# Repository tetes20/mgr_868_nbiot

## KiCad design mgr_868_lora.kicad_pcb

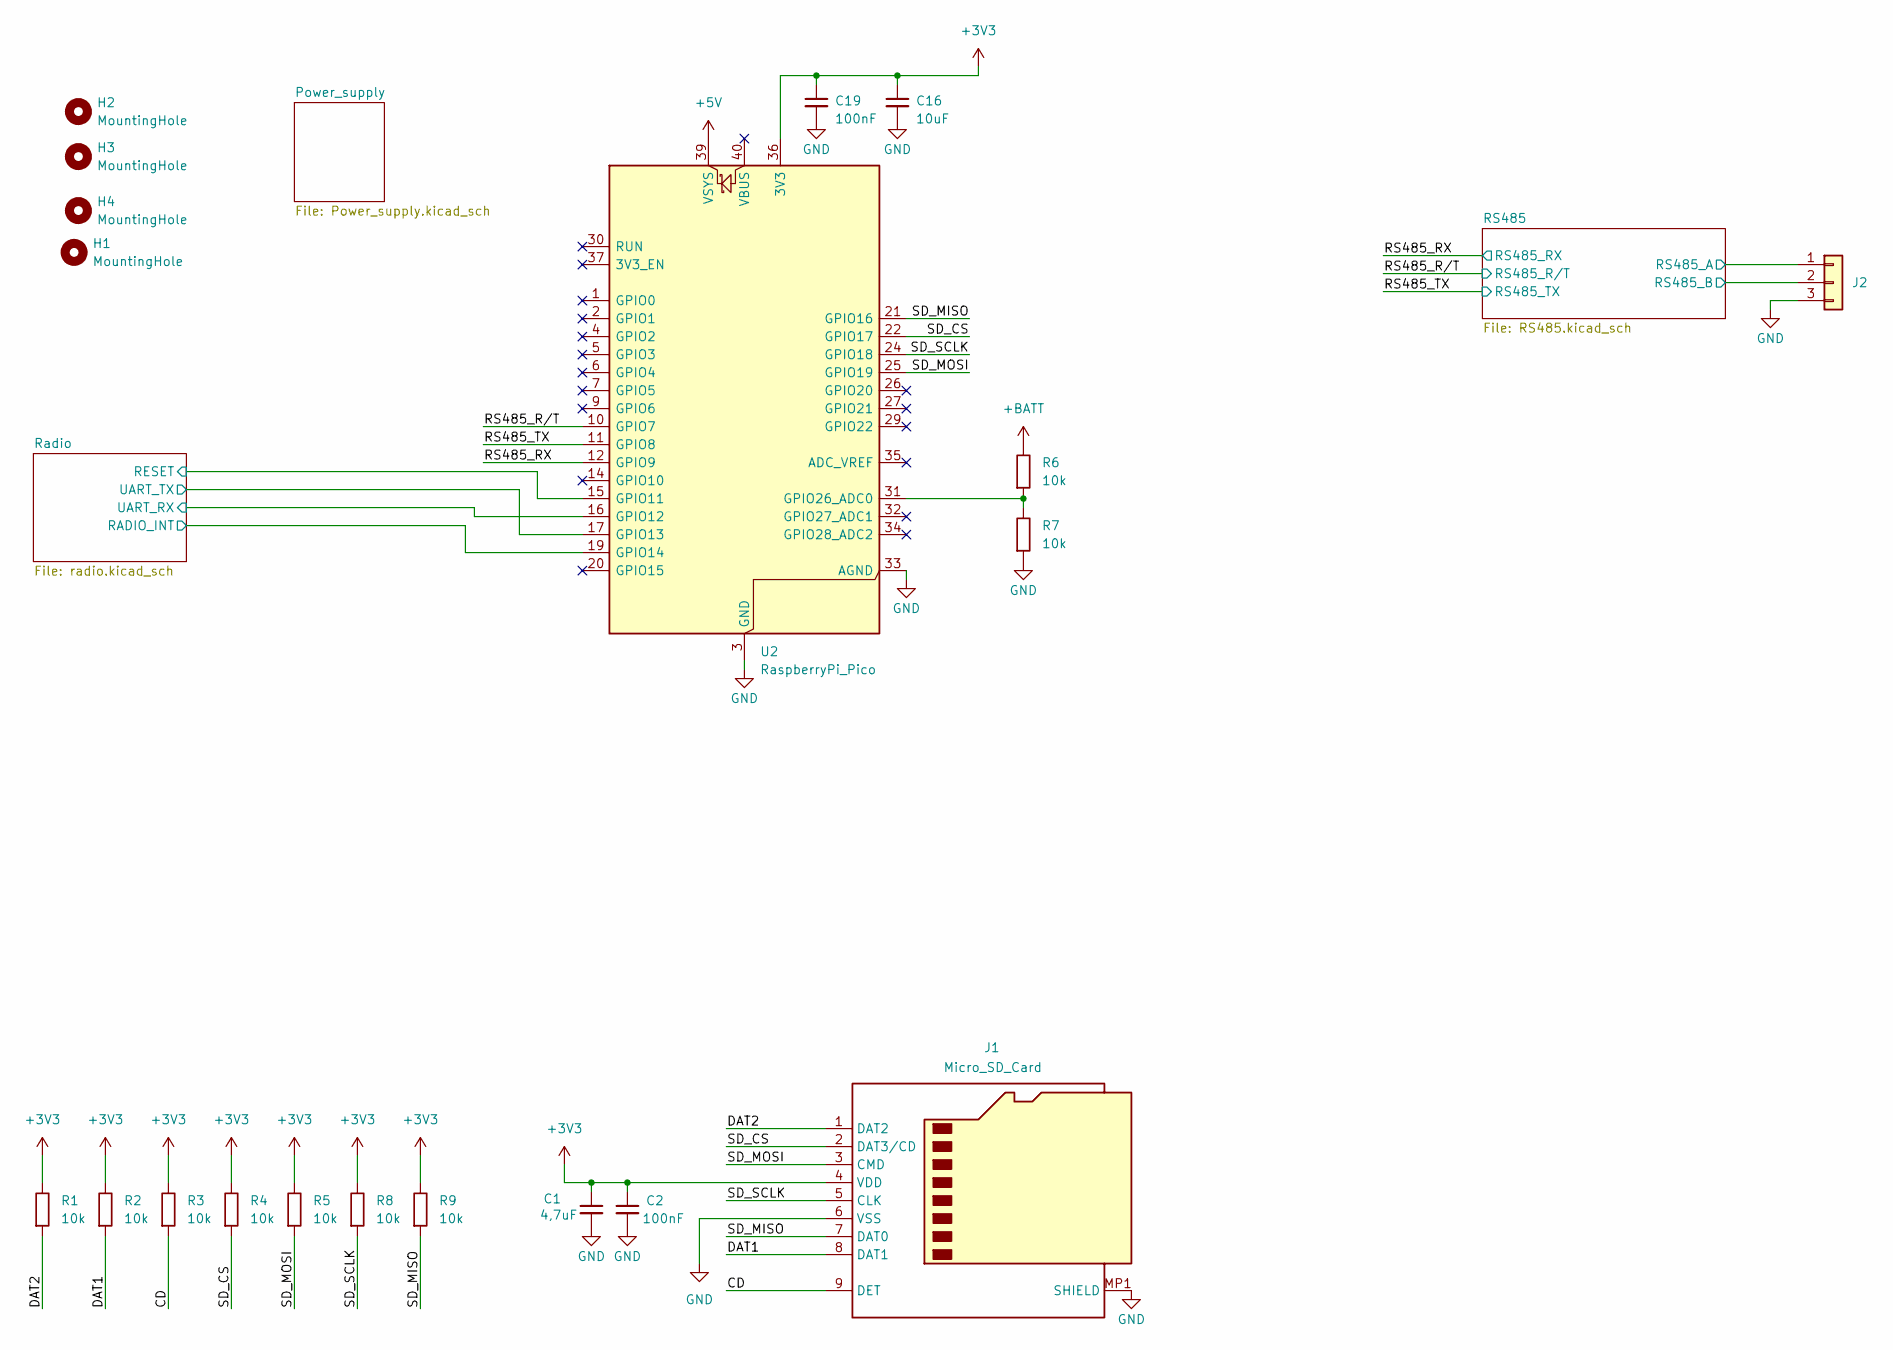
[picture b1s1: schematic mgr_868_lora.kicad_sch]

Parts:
C1: 4,7uF; C_0603_1608Metric_Pad1.08x0.95mm_HandSolder; LCSC C19666
C2: 100nF; C_0603_1608Metric_Pad1.08x0.95mm_HandSolder; LCSC C14663
C16: 10uF; C_0603_1608Metric_Pad1.08x0.95mm_HandSolder
C19: 100nF; C_0603_1608Metric_Pad1.08x0.95mm_HandSolder
H1, H2, H3, H4: MountingHole; MountingHole_3.2mm_M3
J1: Micro_SD_Card; MCSPQ08ASGTR
J2: Conn_01x03; PinHeader_1x03_P2.54mm_Horizontal
R1, R2, R3, R4, R5, R6, R7, R8, R9: 10k; R_0603_1608Metric_Pad0.98x0.95mm_HandSolder; LCSC C25804
U2: RaspberryPi_Pico; RaspberryPi_Pico_Common_Unspecified

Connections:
+3V3: C1.1, C2.1, C16.1, C19.1, J1.4 (VDD), R1.2, R2.2, R3.2, R4.2, R5.2, R8.2, R9.2, U2.36 (3V3); also elsewhere on the board
+5V: U2.39 (VSYS); also elsewhere on the board
+BATT: R6.2; also elsewhere on the board
/CD: J1.9 (DET), R3.1
/DAT1: J1.8 (DAT1), R2.1
/DAT2: J1.1 (DAT2), R1.1
/RS485/RS485_A: J2.1; also elsewhere on the board
/RS485/RS485_B: J2.2; also elsewhere on the board
/RS485_RX: U2.12 (GPIO9); also elsewhere on the board
/RS485_R/T: U2.10 (GPIO7); also elsewhere on the board
/RS485_TX: U2.11 (GPIO8); also elsewhere on the board
/Radio/RADIO_INT: U2.19 (GPIO14); also elsewhere on the board
/Radio/RESET: U2.15 (GPIO11); also elsewhere on the board
/Radio/UART_RX: U2.16 (GPIO12); also elsewhere on the board
/Radio/UART_TX: U2.17 (GPIO13); also elsewhere on the board
/SD_CS: J1.2 (DAT3/CD), R4.1, U2.22 (GPIO17)
/SD_MISO: J1.7 (DAT0), R9.1, U2.21 (GPIO16)
/SD_MOSI: J1.3 (CMD), R5.1, U2.25 (GPIO19)
/SD_SCLK: J1.5 (CLK), R8.1, U2.24 (GPIO18)
GND: C1.2, C2.2, C16.2, C19.2, J1.6 (VSS), J1.MP1 (SHIELD), J1.MP2 (SHIELD), J1.MP3 (SHIELD), J1.MP4 (SHIELD), J2.3, R7.1, U2.3 (GND), U2.8 (GND), U2.13 (GND), U2.18 (GND), U2.23 (GND), U2.28 (GND), U2.33 (AGND), U2.38 (GND); also elsewhere on the board
unnamed: R6.1, R7.2, U2.31 (GPIO26_ADC0)

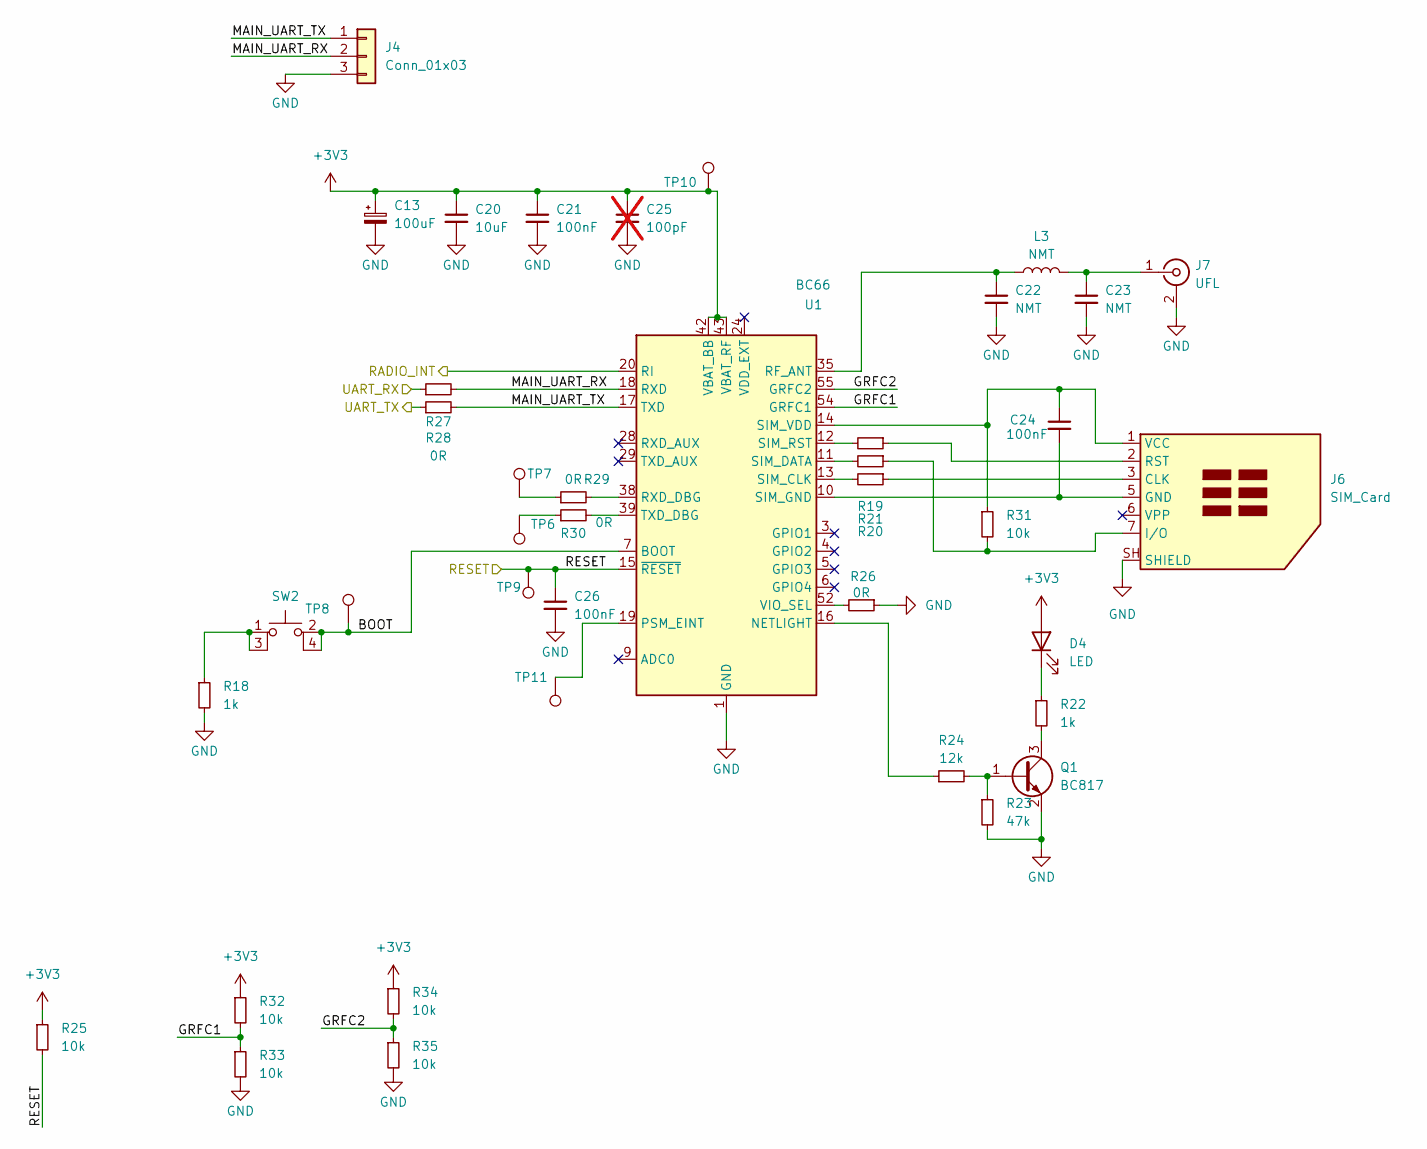
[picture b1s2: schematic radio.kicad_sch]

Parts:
C13: 100uF; CP_EIA-7343-31_Kemet-D_Pad2.25x2.55mm_HandSolder
C20: 10uF; C_0603_1608Metric_Pad1.08x0.95mm_HandSolder
C21, C24, C26: 100nF; C_0603_1608Metric_Pad1.08x0.95mm_HandSolder
C22, C23: NMT; C_0402_1005Metric
C25: 100pF; C_0603_1608Metric_Pad1.08x0.95mm_HandSolder; not fitted
D4: LED; LED_0603_1608Metric
J4: Conn_01x03; PinHeader_1x03_P2.54mm_Horizontal
J6: SIM_Card; nanoSIM_GCT_SIM8060-6-0-14-00
J7: UFL; U.FL_Hirose_U.FL-R-SMT-1_Vertical
L3: NMT; L_0402_1005Metric
Q1: BC817; SOT-23
R18, R22: 1k; R_0603_1608Metric
R19, R20, R21: 22R; R_0603_1608Metric
R23: 47k; R_0603_1608Metric
R24: 12k; R_0603_1608Metric
R25, R31, R32, R33, R34, R35: 10k; R_0603_1608Metric
R26: 0R; R_0402_1005Metric_Pad0.72x0.64mm_HandSolder
R27, R28, R29, R30: 0R; R_0603_1608Metric
SW2: SW_MEC_5E; SW_SPST_SKQG_WithStem
TP6, TP7, TP8, TP9, TP10, TP11: TestPoint; TestPoint_Pad_D1.5mm
U1: BC66; Quectel_BC66

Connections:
+3V3: C13.1, C20.1, C21.1, C25.1, D4.2 (A), R25.1, R32.1, R34.1, TP10.1, U1.42 (VBAT_BB), U1.43 (VBAT_RF); also elsewhere on the board
/Radio/BOOT: SW2.2 (A), SW2.4, TP8.1, U1.7 (BOOT)
/Radio/GRFC1: R32.2, R33.1, U1.54 (GRFC1)
/Radio/GRFC2: R34.2, R35.1, U1.55 (GRFC2)
/Radio/MAIN_UART_RX: J4.2, R27.2, U1.18 (RXD)
/Radio/MAIN_UART_TX: J4.1, R28.2, U1.17 (TXD)
/Radio/RADIO_INT: U1.20 (RI); also elsewhere on the board
/Radio/RESET: C26.1, R25.2, TP9.1, U1.15 (~RESET); also elsewhere on the board
/Radio/UART_RX: R27.1; also elsewhere on the board
/Radio/UART_TX: R28.1; also elsewhere on the board
GND: C13.2, C20.2, C21.2, C22.2, C23.2, C25.2, C26.2, J4.3, J6.SH (SHIELD), J7.2 (Ext), Q1.2 (E), R18.2, R23.2, R26.1, R33.2, R35.2, U1.1 (GND), U1.27 (GND), U1.34 (GND), U1.36 (GND), U1.37 (GND), U1.40 (GND), U1.41 (GND); also elsewhere on the board
unnamed: D4.1 (K), R22.1
unnamed: J6.3 (CLK), R20.1
unnamed: C24.2, J6.5 (GND), U1.10 (SIM_GND)
unnamed: J6.7 (I/O), R21.1, R31.2
unnamed: J6.2 (RST), R19.1
unnamed: C24.1, J6.1 (VCC), R31.1, U1.14 (SIM_VDD)
unnamed: C23.1, J7.1 (In), L3.2
unnamed: Q1.1 (B), R23.1, R24.2
unnamed: Q1.3 (C), R22.2
unnamed: R18.1, SW2.1, SW2.3
unnamed: R29.1, TP7.1
unnamed: R30.1, TP6.1
unnamed: R24.1, U1.16 (NETLIGHT)
unnamed: TP11.1, U1.19 (PSM_EINT)
unnamed: C22.1, L3.1, U1.35 (RF_ANT)
unnamed: R29.2, U1.38 (RXD_DBG)
unnamed: R20.2, U1.13 (SIM_CLK)
unnamed: R21.2, U1.11 (SIM_DATA)
unnamed: R19.2, U1.12 (SIM_RST)
unnamed: R30.2, U1.39 (TXD_DBG)
unnamed: R26.2, U1.52 (VIO_SEL)

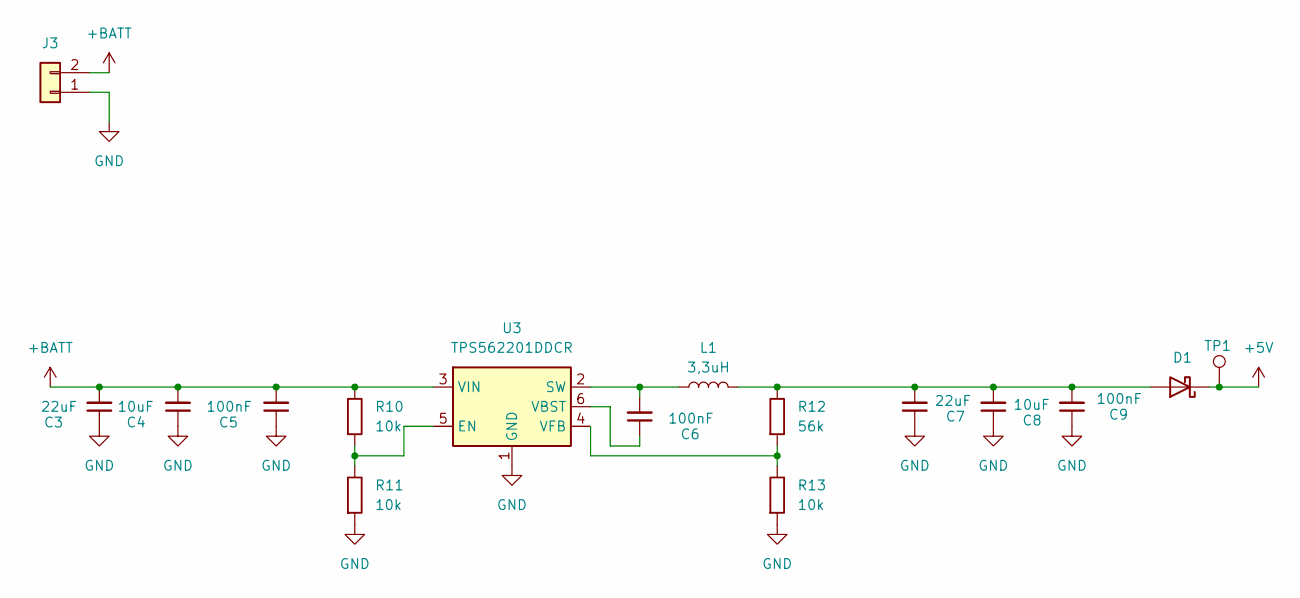
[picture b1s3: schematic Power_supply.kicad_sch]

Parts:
C3, C7: 22uF; C_0805_2012Metric_Pad1.18x1.45mm_HandSolder; LCSC C96446
C4, C8: 10uF; C_0603_1608Metric_Pad1.08x0.95mm_HandSolder; LCSC C45783
C5, C6, C9: 100nF; C_0603_1608Metric_Pad1.08x0.95mm_HandSolder; LCSC C14663
D1: D_Schottky; D_SOD-123F
J3: Conn_01x02; PinHeader_1x02_P2.54mm_Horizontal
L1: 3,3uH; HPI0-3R3; LCSC C408410
R10, R11, R13: 10k; R_0603_1608Metric_Pad0.98x0.95mm_HandSolder; LCSC C25804
R12: 56k; R_0603_1608Metric_Pad0.98x0.95mm_HandSolder
TP1: TestPoint; TestPoint_Pad_D2.0mm
U3: TPS562201DDCR; SOT-23-6_Handsoldering; LCSC C90061

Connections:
+5V: D1.1 (K), TP1.1; also elsewhere on the board
+BATT: C3.2, C4.2, C5.2, J3.2, R10.2, U3.3 (VIN); also elsewhere on the board
GND: C3.1, C4.1, C5.1, C7.1, C8.1, C9.1, J3.1, R11.1, R13.1, U3.1 (GND); also elsewhere on the board
unnamed: C7.2, C8.2, C9.2, D1.2 (A), L1.2, R12.2
unnamed: R10.1, R11.2, U3.5 (EN)
unnamed: C6.2, L1.1, U3.2 (SW)
unnamed: C6.1, U3.6 (VBST)
unnamed: R12.1, R13.2, U3.4 (VFB)

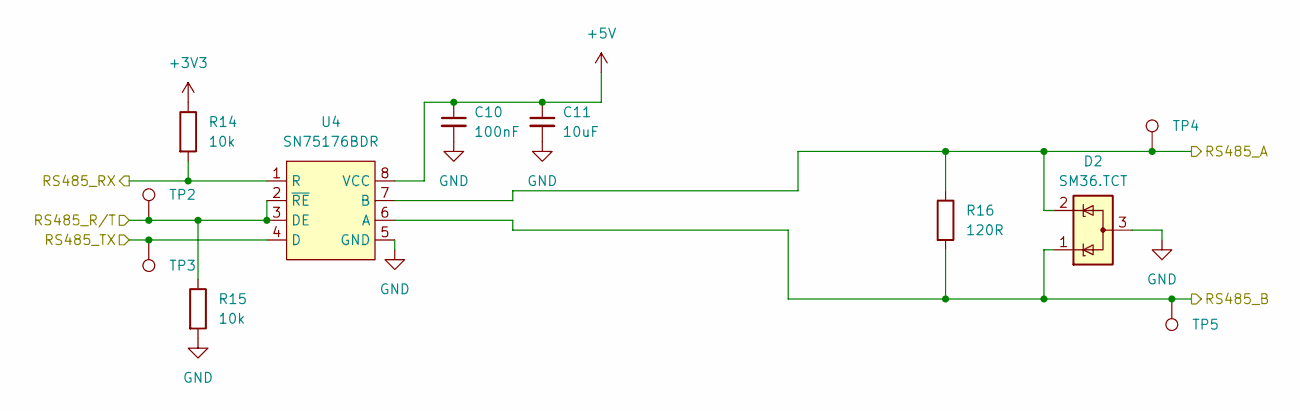
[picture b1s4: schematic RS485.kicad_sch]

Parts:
C10: 100nF; C_0603_1608Metric_Pad1.08x0.95mm_HandSolder
C11: 10uF; C_0603_1608Metric_Pad1.08x0.95mm_HandSolder
D2: SM36.TCT; SOT-23
R14, R15: 10k; R_0603_1608Metric_Pad0.98x0.95mm_HandSolder
R16: 120R; R_0603_1608Metric_Pad0.98x0.95mm_HandSolder
TP2, TP3, TP4, TP5: TestPoint; TestPoint_Pad_D1.5mm
U4: SN75176BDR; SO-8_3.9x4.9mm_P1.27mm

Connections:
+3V3: R14.1; also elsewhere on the board
+5V: C10.1, C11.1, U4.8 (VCC); also elsewhere on the board
/RS485/RS485_A: D2.2 (K), R16.1, TP4.1, U4.7 (B); also elsewhere on the board
/RS485/RS485_B: D2.1 (K), R16.2, TP5.1, U4.6 (A); also elsewhere on the board
/RS485_RX: R14.2, U4.1 (R); also elsewhere on the board
/RS485_R/T: R15.1, TP2.1, U4.2 (~RE), U4.3 (DE); also elsewhere on the board
/RS485_TX: TP3.1, U4.4 (D); also elsewhere on the board
GND: C10.2, C11.2, D2.3 (A), R15.2, U4.5 (GND); also elsewhere on the board

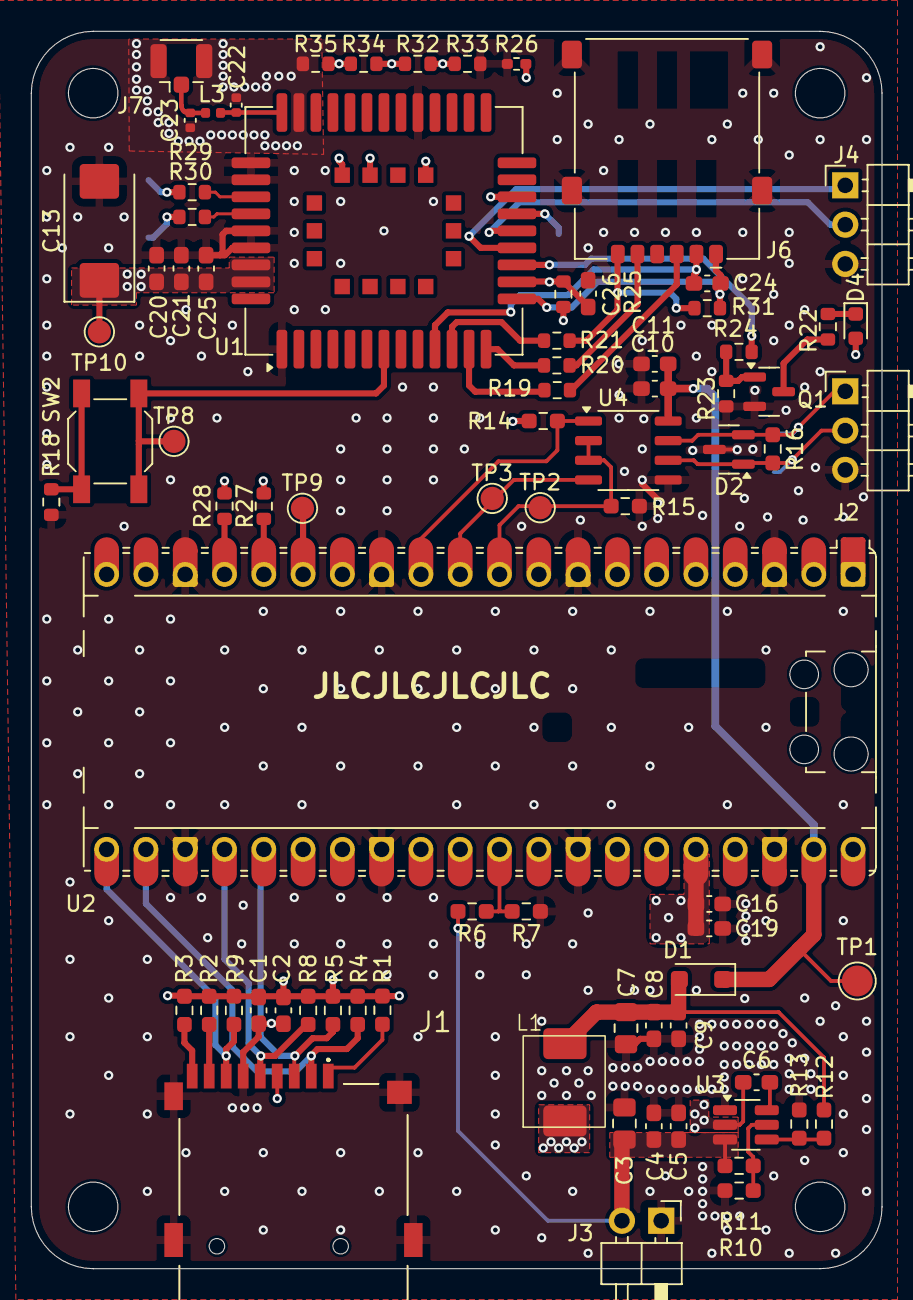
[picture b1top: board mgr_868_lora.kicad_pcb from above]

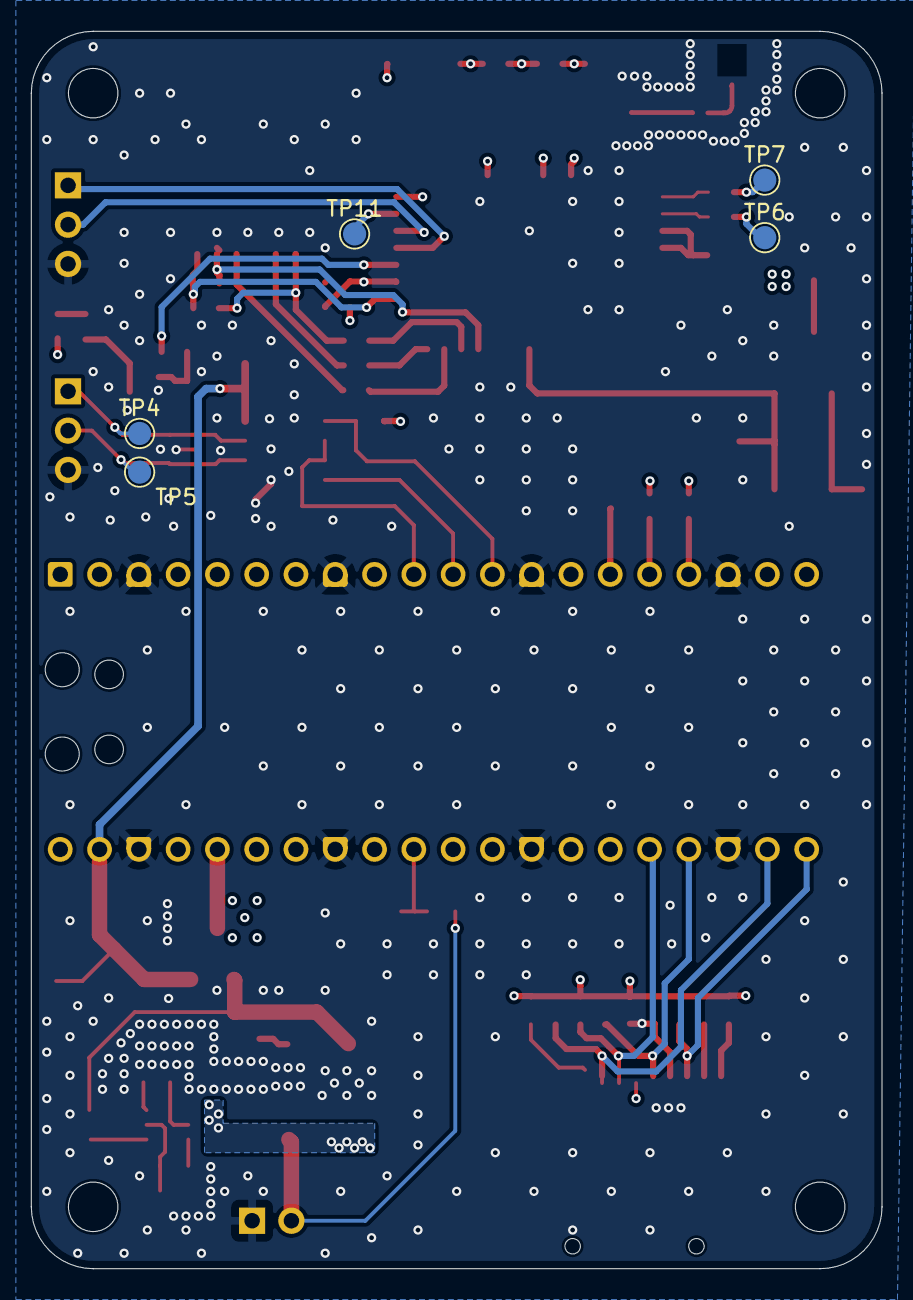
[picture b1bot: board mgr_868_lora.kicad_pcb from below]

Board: 4 copper layers, 55.0 x 80.0 mm, 87 parts (5 on the bottom side), 52 nets.

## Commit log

2025-03-18 init commit
2025-03-18 to review
2025-03-18 added schematic and pcb pdf
